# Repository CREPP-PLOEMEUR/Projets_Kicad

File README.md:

# Projets_Kicad
Un répertoire contenant les projets réalisés lors de l'atelier Conception Electronique

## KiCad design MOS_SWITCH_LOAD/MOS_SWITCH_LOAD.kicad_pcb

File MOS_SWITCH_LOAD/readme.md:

Un module pour commuter une alimentation sur le rail positif.

<!-- AUTEUR : Nicolas LE GUERROUE -->
<!-- DATE : 2024 -->

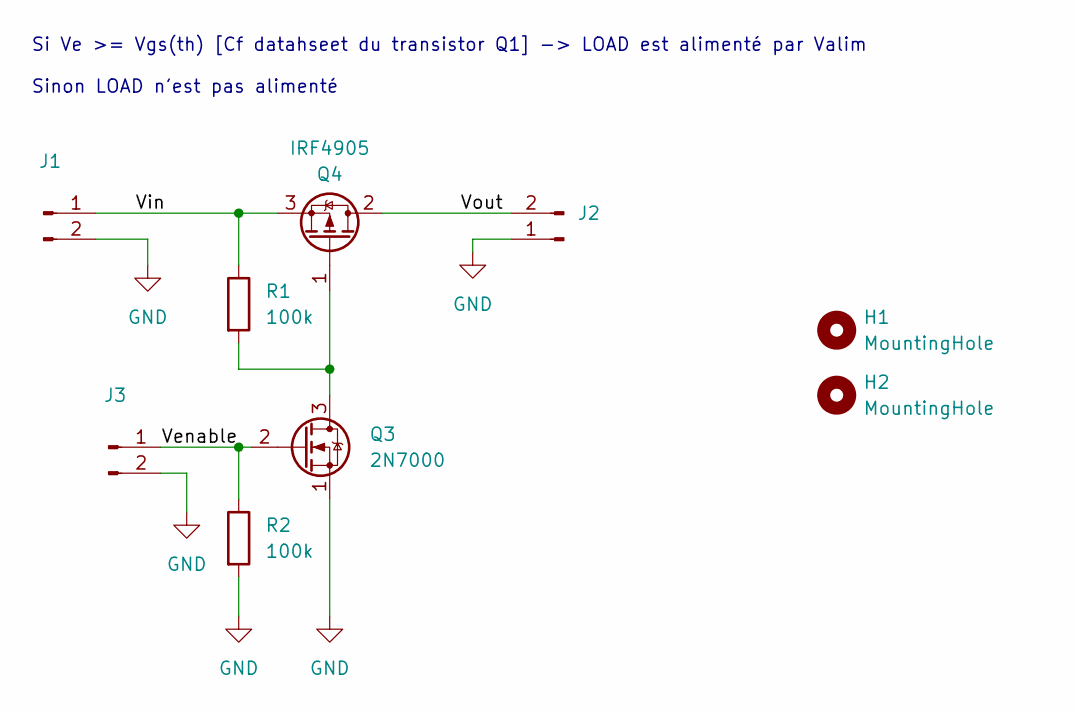
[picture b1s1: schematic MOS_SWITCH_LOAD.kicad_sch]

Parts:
H1, H2: MountingHole; MountingHole_3mm
J1, J2, J3: Conn_01x02_Pin; TerminalBlock_TE_282834-2_1x02_P2.54mm_Horizontal
Q3: 2N7000; TO-92_Inline
Q4: IRF4905; TO-220-3_Vertical
R1, R2: 100k; R_Axial_DIN0207_L6.3mm_D2.5mm_P7.62mm_Horizontal

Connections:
GND: J1.2, J2.1, J3.2, Q3.1 (S), R2.2
unnamed: J1.1, Q4.3 (S), R1.1
unnamed: J2.2, Q4.2 (D)
unnamed: J3.1, Q3.2 (G), R2.1
unnamed: Q3.3 (D), Q4.1 (G), R1.2

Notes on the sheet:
Si Ve >= Vgs(th) [Cf datahseet du transistor Q1] -> LOAD est alimenté par Valim Sinon LOAD n'est pas alimenté

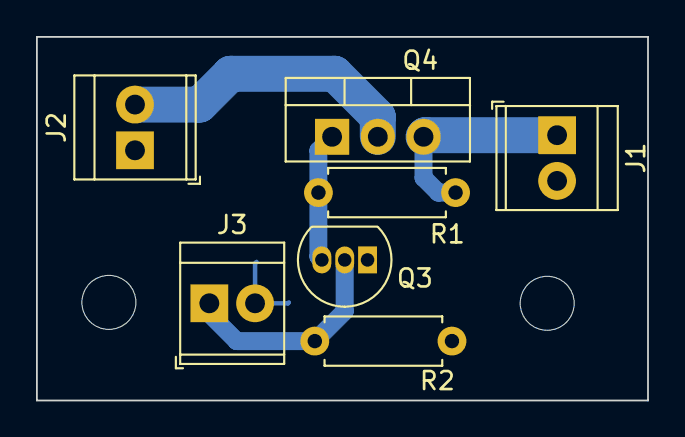
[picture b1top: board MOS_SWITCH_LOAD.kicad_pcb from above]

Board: 2 copper layers, 34.0 x 20.2 mm, 9 parts (0 on the bottom side), 5 nets.

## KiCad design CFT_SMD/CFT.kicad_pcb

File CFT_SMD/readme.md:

Un convertisseur Fréquence-Tension pour le Tracker solaire.
Son application vise à connaître la vitesse du vent en fonction de la fréquence d'un anémomètre.
<!-- AUTEUR : Nicolas LE GUERROUE -->
<!-- DATE : 2024 -->

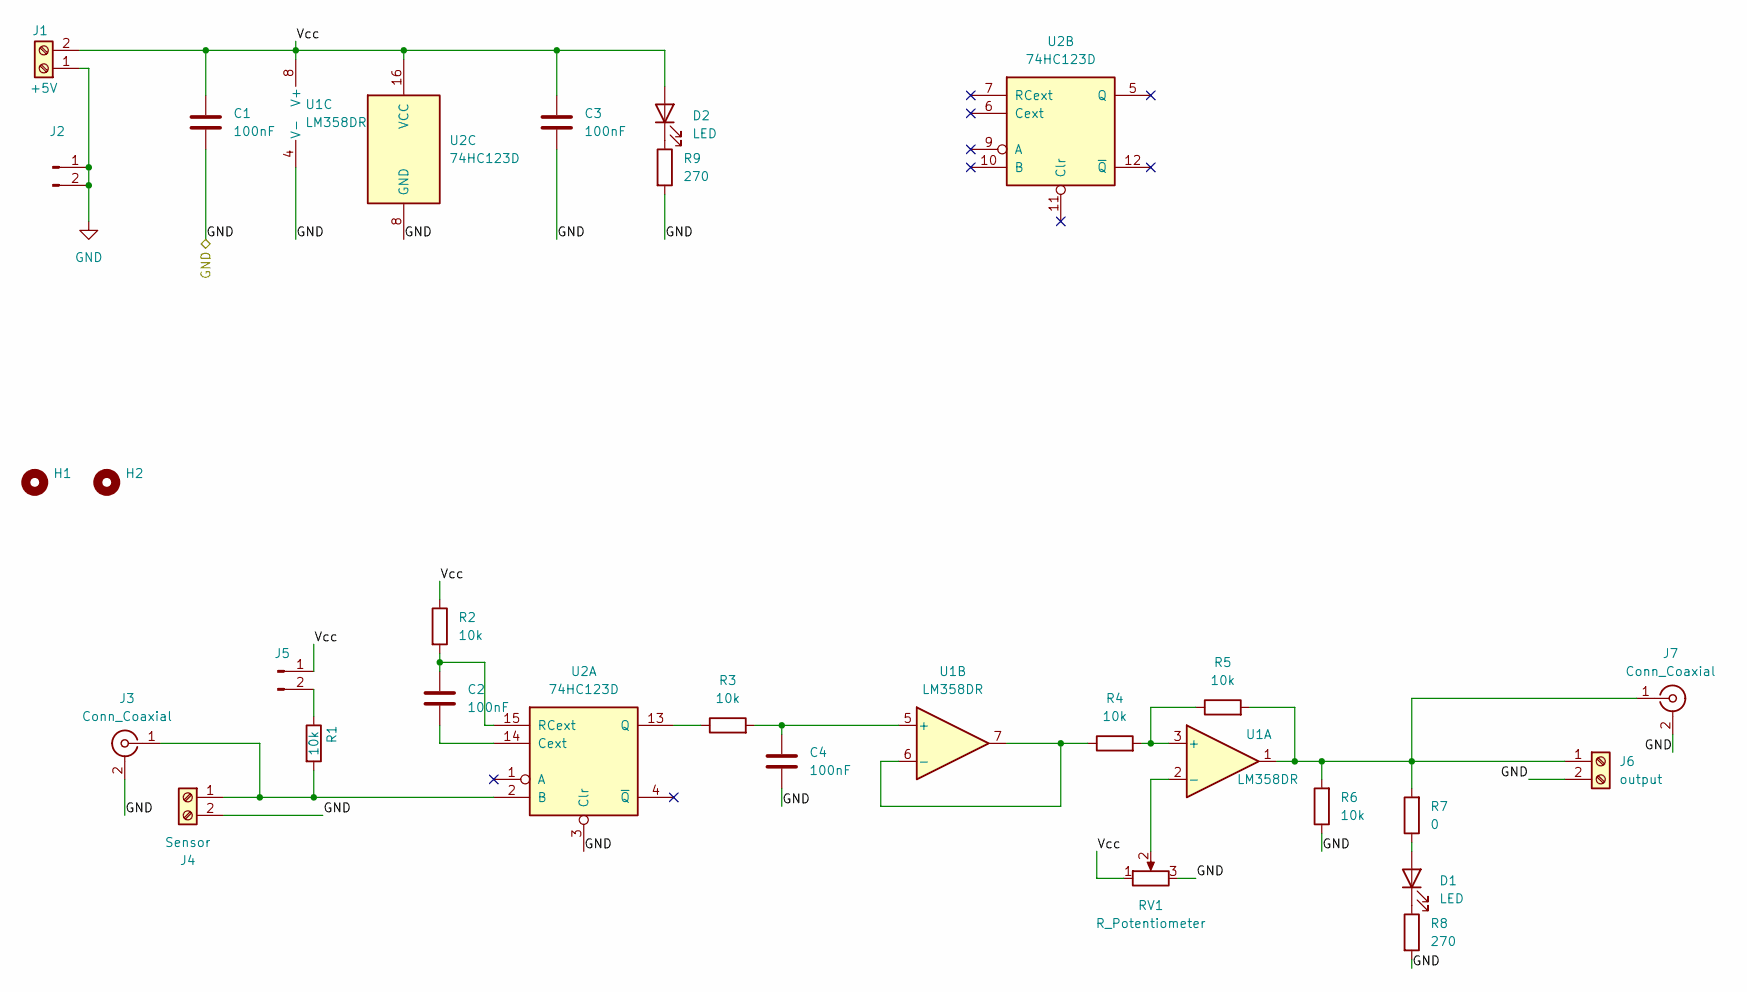
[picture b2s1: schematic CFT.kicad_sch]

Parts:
C1, C2, C3, C4: 100nF; C_0603_1608Metric
D1, D2: LED; LED_0603_1608Metric
H1, H2: MountingHole; MountingHole_3mm
J1: +5V; TerminalBlock_TE_282834-2_1x02_P2.54mm_Horizontal
J2: GND; PinHeader_1x02_P2.54mm_Vertical
J3, J7: Conn_Coaxial; BNC_Amphenol_B6252HB-NPP3G-50_Horizontal
J4: Sensor; TerminalBlock_TE_282834-2_1x02_P2.54mm_Horizontal
J5: LINK_Power; PinHeader_1x02_P2.54mm_Vertical
J6: output; TerminalBlock_TE_282834-2_1x02_P2.54mm_Horizontal
R1, R2, R3, R4, R5, R6: 10k; R_0603_1608Metric
R7: 0; R_0603_1608Metric
R8, R9: 270; R_0603_1608Metric
RV1: R_Potentiometer; Potentiometer_Bourns_3314J_Vertical
U1: LM358DR; TSSOP-8_3x3mm_P0.65mm
U2: 74HC123D; SOIC-16W_5.3x10.2mm_P1.27mm

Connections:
/Vcc: C1.1, C3.1, D2.2 (A), J1.2, J5.1, R2.1, RV1.1, U1.8 (V+), U2.16 (VCC)
GND: C1.2, C3.2, C4.2, J1.1, J2.1, J2.2, J3.2 (Ext), J4.2, J6.2, J7.2 (Ext), R6.1, R8.2, R9.2, RV1.3, U1.4 (V-), U2.3 (Clr), U2.8 (GND)
unnamed: D1.2 (A), R7.1
unnamed: D1.1 (K), R8.1
unnamed: D2.1 (K), R9.1
unnamed: J3.1 (In), J4.1, R1.2, U2.2 (B)
unnamed: J5.2, R1.1
unnamed: J6.1, J7.1 (In), R5.2, R6.2, R7.2, U1.1
unnamed: R4.2, R5.1, U1.3 (+)
unnamed: RV1.2, U1.2 (-)
unnamed: C4.1, R3.2, U1.5 (+)
unnamed: R4.1, U1.6 (-), U1.7
unnamed: C2.2, U2.14 (Cext)
unnamed: R3.1, U2.13 (Q)
unnamed: C2.1, R2.2, U2.15 (RCext)

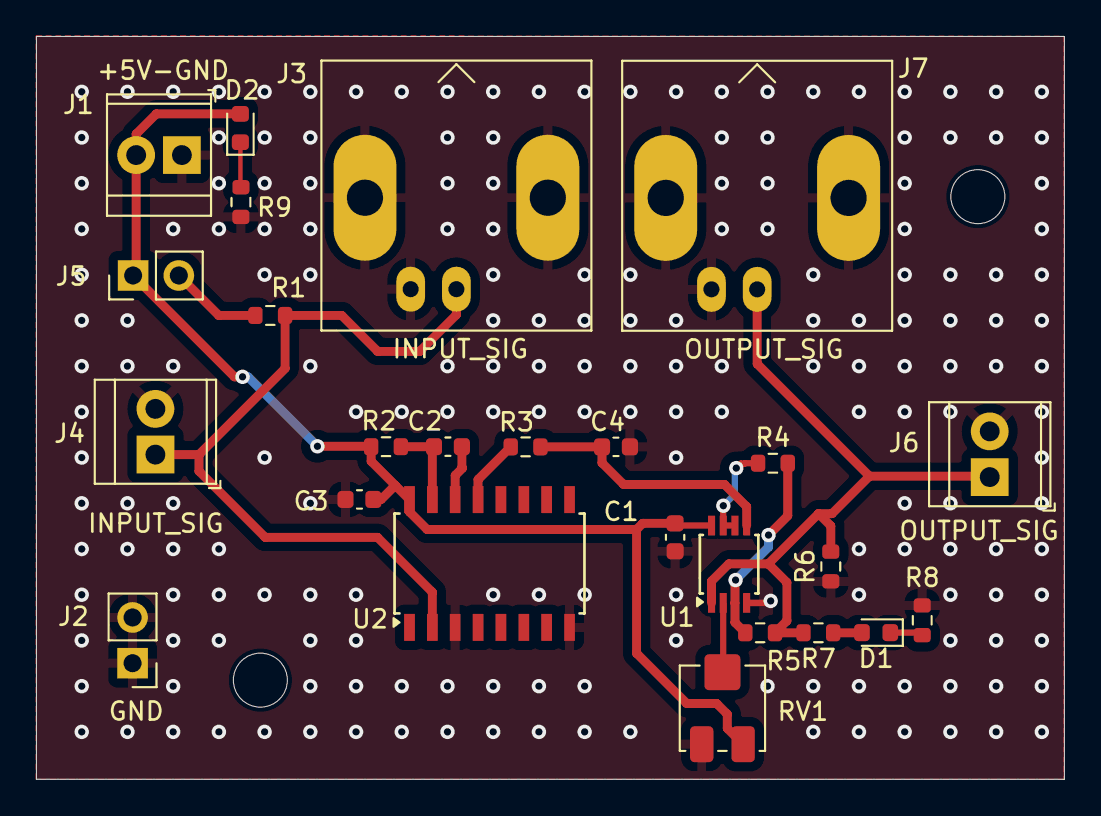
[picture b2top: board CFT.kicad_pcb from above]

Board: 2 copper layers, 57.1 x 41.3 mm, 27 parts (0 on the bottom side), 15 nets.

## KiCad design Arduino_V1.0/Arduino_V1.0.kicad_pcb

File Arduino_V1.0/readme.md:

Un carte Arduino fait-maison, avec l'essentiel pour son bon fonctionnement.
Cette version n'intègre pas de régulateur de tension.

<!-- AUTEUR : Nicolas LE GUERROUE -->
<!-- DATE : 2023 -->

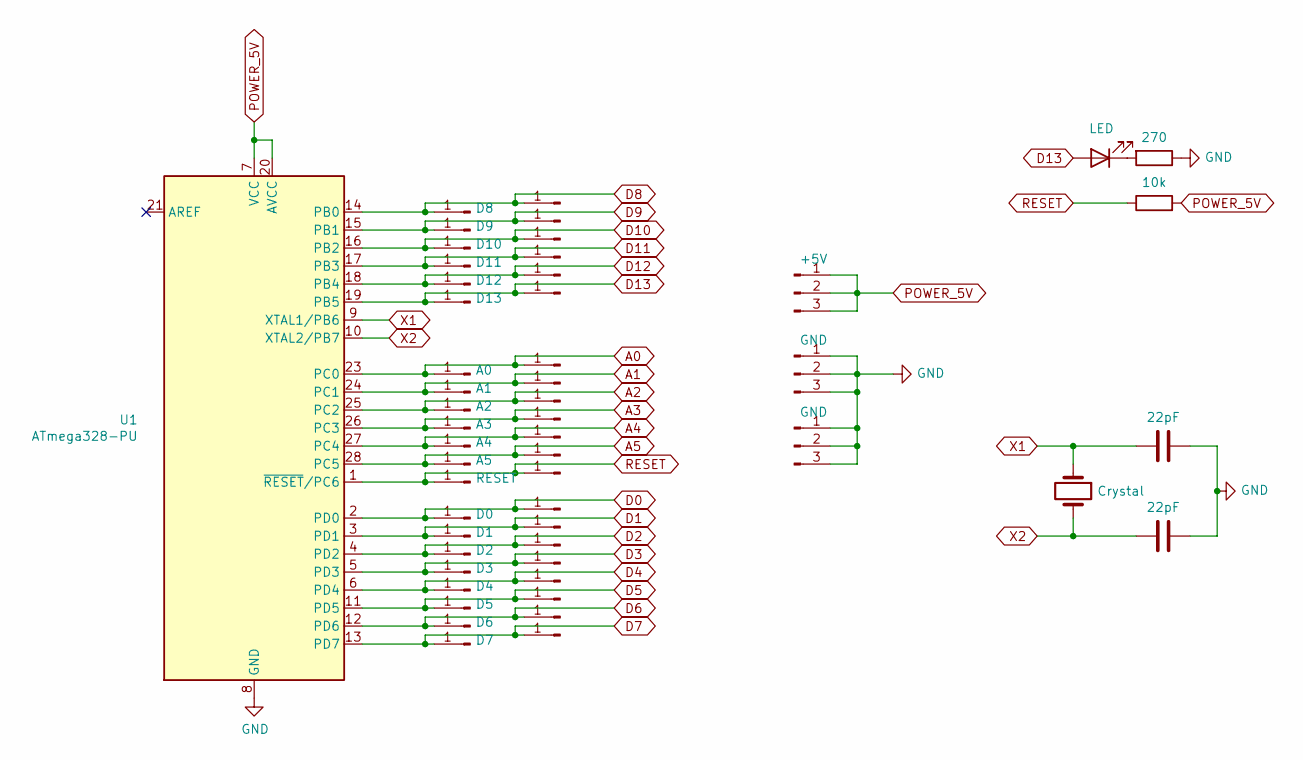
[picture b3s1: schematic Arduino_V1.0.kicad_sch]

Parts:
C1, C2: 22pF; C_Disc_D3.0mm_W1.6mm_P2.50mm
D1: LED; LED_D5.0mm
J1: +5V; PinHeader_1x03_P2.54mm_Vertical
J2, J45: GND; PinHeader_1x03_P2.54mm_Vertical
J3: D8; PinHeader_1x03_P2.54mm_Vertical
J4: D9; PinHeader_1x01_P2.54mm_Vertical
J5: D10; PinHeader_1x01_P2.54mm_Vertical
J6: D11; PinHeader_1x01_P2.54mm_Vertical
J7: D12; PinHeader_1x01_P2.54mm_Vertical
J8: D13; PinHeader_1x01_P2.54mm_Vertical
J9: A0; PinHeader_1x01_P2.54mm_Vertical
J10: A1; PinHeader_1x01_P2.54mm_Vertical
J11: A2; PinHeader_1x01_P2.54mm_Vertical
J12: A3; PinHeader_1x01_P2.54mm_Vertical
J13: A4; PinHeader_1x01_P2.54mm_Vertical
J14: A5; PinHeader_1x01_P2.54mm_Vertical
J15: RESET; PinHeader_1x01_P2.54mm_Vertical
J16: D0; PinHeader_1x01_P2.54mm_Vertical
J17: D1; PinHeader_1x01_P2.54mm_Vertical
J18: D2; PinHeader_1x01_P2.54mm_Vertical
J19: D3; PinHeader_1x01_P2.54mm_Vertical
J20: D4; PinHeader_1x01_P2.54mm_Vertical
J21: D5; PinHeader_1x01_P2.54mm_Vertical
J22: D6; PinHeader_1x01_P2.54mm_Vertical
J23: D7; PinHeader_1x01_P2.54mm_Vertical
J24, J25, J26, J27, J28, J29, J30, J31, J32, J33, J34, J35, J36, J37, J38, J39, J40, J41, J42, J43, J44: D8; PinHeader_1x01_P2.54mm_Vertical
R1: 270; R_Axial_DIN0207_L6.3mm_D2.5mm_P10.16mm_Horizontal
R2: 10k; R_Axial_DIN0207_L6.3mm_D2.5mm_P10.16mm_Horizontal
U1: ATmega328-PU; DIP-28_W7.62mm
Y1: Crystal; Crystal_HC49-4H_Vertical

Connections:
A0: J9.1, J30.1, U1.23 (PC0)
A1: J10.1, J31.1, U1.24 (PC1)
A2: J11.1, J32.1, U1.25 (PC2)
A3: J12.1, J33.1, U1.26 (PC3)
A4: J13.1, J34.1, U1.27 (PC4)
A5: J14.1, J35.1, U1.28 (PC5)
D0: J16.1, J37.1, U1.2 (PD0)
D1: J17.1, J38.1, U1.3 (PD1)
D2: J18.1, J39.1, U1.4 (PD2)
D3: J19.1, J40.1, U1.5 (PD3)
D4: J20.1, J41.1, U1.6 (PD4)
D5: J21.1, J42.1, U1.11 (PD5)
D6: J22.1, J43.1, U1.12 (PD6)
D7: J23.1, J44.1, U1.13 (PD7)
D8: J3.1, J24.1, U1.14 (PB0)
D9: J4.1, J25.1, U1.15 (PB1)
D10: J5.1, J26.1, U1.16 (PB2)
D11: J6.1, J27.1, U1.17 (PB3)
D12: J7.1, J28.1, U1.18 (PB4)
D13: D1.2 (A), J8.1, J29.1, U1.19 (PB5)
GND: C1.1, C2.1, J2.1, J2.2, J2.3, J45.1, J45.2, J45.3, R1.1, U1.8 (GND), U1.22 (GND)
unnamed: D1.1 (K), R1.2
POWER_5V: J1.1, J1.2, J1.3, R2.2, U1.7 (VCC), U1.20 (AVCC)
RESET: J15.1, J36.1, R2.1, U1.1 (~RESET/PC6)
X1: C1.2, U1.9 (XTAL1/PB6), Y1.1
X2: C2.2, U1.10 (XTAL2/PB7), Y1.2

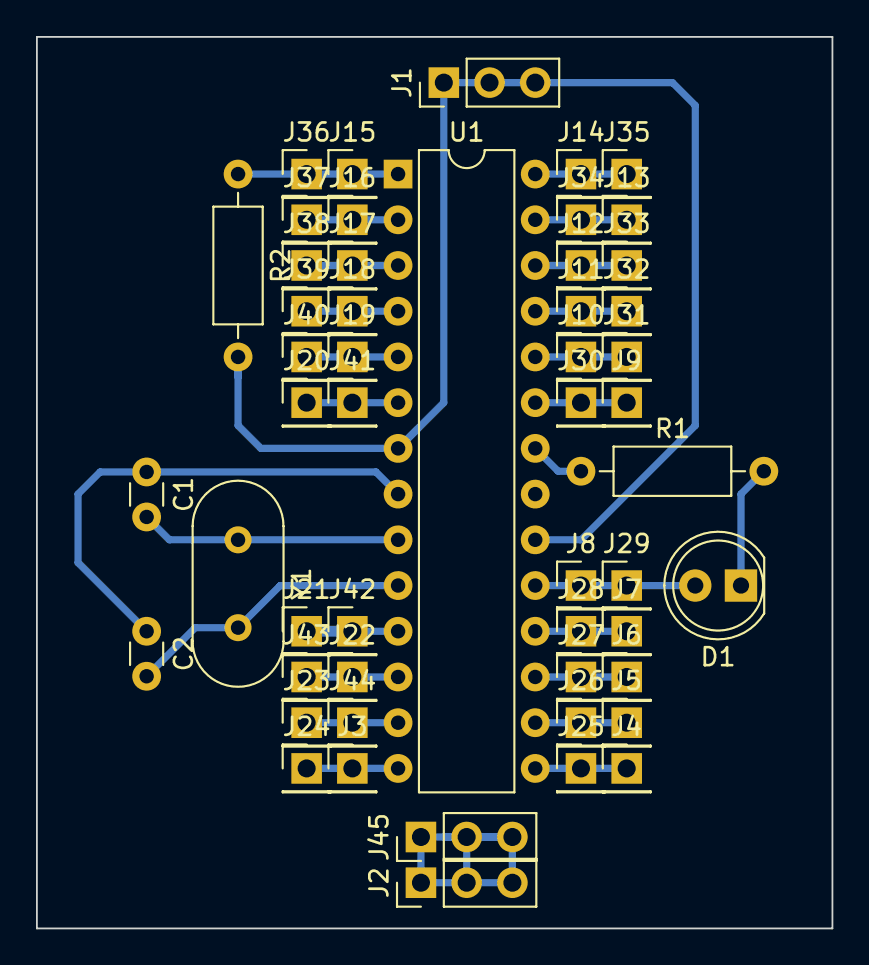
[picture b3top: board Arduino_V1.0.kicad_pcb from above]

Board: 2 copper layers, 44.2 x 49.5 mm, 52 parts (0 on the bottom side), 26 nets.

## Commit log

2024-07-27 Add file
2024-07-27 Update zip
2024-07-27 Add img
2024-07-27 update date, author
2024-07-27 Add tracker
2024-07-27 update of directory
